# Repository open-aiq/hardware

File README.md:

# Open AIQ hardware

PCB designs (KiCad) for the Open AIQ air-quality monitor.
Firmware lives in [open-aiq/device](https://github.com/open-aiq/device); its
[`src/board.rs`](https://github.com/open-aiq/device/blob/main/src/board.rs) is the source of truth for the GPIO map.

## Layout

| Path | Contents |
| --- | --- |
| `pcb/proto2/` | Prototype 2: carrier PCB for the ESP32-S3 devkit with sensor connectors |
| `lib/` | Our own symbols and footprints, shared by every board |
| `scripts/` | `export.sh`, which builds a board's outputs from the command line |

Each PCB folder holds the KiCad project, the schematic and assembly PDFs, and
the fabrication outputs (Gerbers and BOM) under `fab/`. Its README
covers the parts, the pin map and what to check before you build.

Still to come: an SMT board with the ESP32-S3 module on it (in progress on the
`smt` branch), a battery-powered revision, and a 3D-printed enclosure.

## Working in KiCad

Everything here is a normal KiCad 10 project, and the KiCad files are the source
of truth. Open `pcb/<board>/<board>.kicad_pro` and edit the schematic and board
as you would any other design.

- **Libraries need no setup.** Our own symbols and footprints live in
  [`lib/`](lib), and each project finds them through `${KIPRJMOD}`. A part we've
  adapted, like the ESP32-S3 module with JLCPCB-sized vias, is saved there under
  its own name, so *Update footprints from library* keeps our changes.
- **Rules live in the project.** Net classes (wider power tracks), clearances and
  via sizes are set in *Board Setup*, so DRC is ready to go. The board opens
  with zero ERC and DRC messages. If you see one, it's new.
- **Outputs come from a jobset.** Open `<board>.kicad_jobset` from the project
  window (or *File → Jobsets*) and run it. It checks ERC and DRC, then writes the
  schematic PDF, an assembly drawing with every reference designator, Gerbers,
  drill files, the BOM and, for the SMT board, placement and JLCPCB BOM files.
- **The command line runs the same jobset.** From the repo root,
  `scripts/export.sh pcb/<board>` runs it with `kicad-cli`, then adds what KiCad
  doesn't make on its own: a zipped Gerber set, a JLCPCB-format placement file
  and 3D renders.

Please commit your KiCad edits and the regenerated outputs together, so the PDFs
and fab files always match the design.

## Roadmap

Planned work is tracked on the [Open AIQ Roadmap](https://github.com/orgs/open-aiq/projects/1) board.

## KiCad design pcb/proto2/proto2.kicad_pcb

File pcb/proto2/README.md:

# Proto2: devkit carrier

Proto2 is the board we use to get Open AIQ off the breadboard. The OLED sits
top-left with three buttons under it, the sensors take the middle, and your
ESP32-S3 devkit plugs into two sockets on the right with its USB port at the
bottom edge. It's single-sided (all copper on the bottom) and everything is
through-hole, so you can solder it by hand and get it made almost anywhere.

| Top | Bottom |
| --- | --- |
|  |  |

## What's on it

| Ref | Part | Wiring |
| --- | --- | --- |
| U1 | ESP32-S3-DevKitC-1, or a pin-compatible clone, on two 1×22 sockets 25.4 mm (1.0 in) apart | All signals are on the left header. USB faces the bottom edge |
| J1 | PMS5003 particulate sensor, 8-pin 1.25 mm connector | 5 V, UART on GPIO 18 (ESP TX) / 17 (ESP RX), SET on GPIO 8, RESET on GPIO 16 |
| J2 | 1.3 in SH1106 128×64 I2C OLED module, 4-pin socket | I2C, `GND VCC SCL SDA` from left to right, the order printed on the module's front. The module lies flat over the dashed OLED area |
| J3 | SHT30 breakout with 6 pins, on a 1×4 and a 1×2 socket | I2C, `VIN GND SCL SDA`. The 2 pins on the far edge (usually ADDR and ALERT) are for support only |
| SW1, SW2, SW3 | Right, left and pair buttons, 6 × 6 mm 4-leg tactile switches | GPIO 15, GPIO 6 and GPIO 7, active-low |
| R1, R2 | 4.7 kΩ I2C pull-ups | SDA (GPIO 5), SCL (GPIO 4) to 3.3 V |
| R3, R4 | 10 kΩ pull-ups | SET (R3) and RESET (R4), so the PMS5003 stays awake and out of reset unless the firmware says otherwise |
| C1–C4 | Bulk and decoupling capacitors | 47 µF + 100 nF on 5 V, 10 µF + 100 nF on 3.3 V |

The pins match [`src/board.rs`](https://github.com/open-aiq/device/blob/main/src/board.rs)
in open-aiq/device. Rev B moved several pins so every trace fits on one side of
the board, so flash firmware with the matching `board.rs` before you plug a
devkit in. Older breadboard builds used the previous map (SDA 8, SCL 9, buttons
4 and 5), which you'll find in the firmware README. A few pins are there for
later:

- **SW3 Pair (GPIO 7)** will start BLE pairing with the phone app. The firmware
  doesn't read it yet, so for now pressing it does nothing.
- **SET and RESET** have pull-ups that keep the sensor running while the
  devkit boots. The firmware drives SET low to rest the sensor between
  readings; RESET isn't driven yet.

The schematic is in [`proto2.pdf`](proto2.pdf), and [`proto2-assembly.pdf`](proto2-assembly.pdf) shows where each part goes.
Wondering why a part is there, or why it has that value?
[`proto2-rationale.pdf`](proto2-rationale.pdf) walks through every component and
pin choice, with references to the datasheets.

## Revisions

- **Rev C** (this one) rotates the OLED socket so it reads `GND VCC SCL SDA`,
  the order printed on the module. Rev B had it mirrored, which would have
  swapped 3.3 V and ground. It also widens the ground tracks where there's
  room and changes C1 from 100 µF to 47 µF. The pin map is the same as rev B.
- **Rev B** made the board single-sided, added the pair button and moved to
  today's pin map.
- **Rev A** was the first, two-layer carrier.

## Before you build

- **Check your OLED's pin order.** The socket reads `GND VCC SCL SDA` from left
  to right, and the silkscreen says so too. Hold your module face-up with its
  pins along the top: its labels should read the same. Some modules swap GND
  and VCC, and plugging one in backwards can damage it.
- **Clone devkits need the 5 V pad bridged.** Many DevKitC-1 clones have an
  `IN-OUT` solder jumper next to the 5V pin. Until you bridge it, USB power
  doesn't reach that pin, and the PMS5003 stays dark. Once it's bridged, don't
  feed 5 V into the pin while USB is plugged in.
- **The OLED lies flat over its dashed area.** It plugs into J2 face-up and
  rests over that area, which is why nothing else is placed there.
- **Measure your SHT30 before you order.** We set the gap between its two pin
  rows to 6.35 mm from a photo. If yours differs, the 4-pin row still works, and
  you can leave the 1×2 socket out.
- **The PMS5003 sits on the marked bed.** Stick it down with double-sided foam
  tape, vents facing the top edge so it doesn't pull in warm air from the
  devkit. Its case is metal, but there's no copper on top, so it can't short
  anything.
- **The devkit's antenna hangs off the top edge.** That's on purpose: copper
  under an antenna weakens WiFi and BLE, so the ground fill also stops short of
  that end.
- **R8 modules use GPIO 35, 36 and 37 for PSRAM.** Proto2 leaves them
  unconnected, so keep it that way if you add anything.
- **The status LED is on the devkit.** The firmware drives both GPIO 48
  (DevKitC-1 v1.0) and GPIO 38 (v1.1), so it lights on either. Proto2 leaves
  both pins free.

## First power-up

A few quick checks before you trust the readings:

1. **Check the PMS5003 cable with a multimeter first.** Pin 1 on the sensor
   should reach pin 1 (5 V) on J1. Some 1.25 mm cables come wired in reverse.
   That won't damage anything, but the sensor stays silent.
2. **Measure 5 V at J1 pin 1 with the fan running.** The PMS5003 needs at least
   4.5 V. A long or thin USB cable, plus the devkit's own power path, can pull
   the 5V pin below what your charger supplies.
3. **Read the serial log.** The I2C scan at boot should find `0x3C` (OLED) and
   `0x44` (SHT30).
4. **Look at the screen.** It should read upright with the pins at the top. If it
   shows upside down, the firmware's display setup notes how to flip it.

## Parts

You'll find the generated list in [`fab/proto2-bom.csv`](fab/proto2-bom.csv).
To buy them:

| Qty | Part | Notes |
| --- | --- | --- |
| 2 | 1×22 female header, 2.54 mm | Sockets for the devkit (U1) |
| 2 | 1×4 female header, 2.54 mm | OLED (J2) and SHT30 (J3) |
| 1 | 1×2 female header, 2.54 mm | SHT30's far-edge pins (J3) |
| 1 | Molex PicoBlade 53047-0810, 8-pin vertical | PMS5003 (J1). Check that it fits your sensor's cable first |
| 3 | 6 × 6 mm through-hole tactile switch, 4-leg (for example Omron B3F-1000) | SW1, SW2, SW3 |
| 2 | 4.7 kΩ resistor, 1/4 W axial | R1, R2 |
| 2 | 10 kΩ resistor, 1/4 W axial | R3, R4 |
| 1 | 47 µF electrolytic, ≥10 V, 6.3 mm radial, 2.5 mm pitch | C1 |
| 1 | 10 µF electrolytic, ≥10 V, 5 mm radial, 2 mm pitch | C3 |
| 2 | 100 nF ceramic, 5 mm pitch | C2, C4 |

## Ordering

[`fab/proto2-gerbers.zip`](fab/proto2-gerbers.zip) holds the Gerbers and
Excellon drill files: bottom copper, bottom solder mask, top silkscreen, the
outline and drills. Upload it to JLCPCB, PCBWay or a local shop as it is. We
haven't placed an order yet, so treat these settings as our first guess:

| Setting | Value |
| --- | --- |
| Size | 142 × 63 mm |
| Layers | Order it as 2-layer: you get plated holes, and the top side has pads only. The copper is all on the bottom, so a 1-layer order works too, but its holes aren't plated and the small PMS5003 connector pads lift easily when you solder them |
| Thickness | 1.6 mm |
| Min track / clearance | 0.3 / 0.25 mm (power 0.8 mm), so a track can pass between two 2.54 mm pins |
| Min hole | 0.5 mm (PMS5003 connector pins); no vias |
| Surface finish | HASL is fine |

Every part is through-hole, so there's no pick-and-place file.

## Editing

Open `proto2.kicad_pro` in KiCad 10. The repo's [Working in KiCad](../../README.md#working-in-kicad)
guide covers libraries, rules and outputs. These are ours, in [`lib/`](../../lib):

- the devkit socket and SHT30 socket footprints. The devkit socket marks its
  GND pins and its two 3V3 pins as joined inside the devkit (KiCad *jumper pad
  groups*), so they don't need tracks between them
- the arrow and phone-with-Bluetooth icons under the buttons, which are
  board-only footprints you can move
- the sensor symbols

To refresh the outputs, run `proto2.kicad_jobset` in KiCad, or this from the repo
root:

```sh
scripts/export.sh pcb/proto2
```

Both stop if ERC or DRC finds a problem.

The design rationale is written in [Typst](https://typst.app). If you change a
part, update `proto2-rationale.typ` too, then rebuild the PDF from this folder:

```sh
typst compile proto2-rationale.typ
```

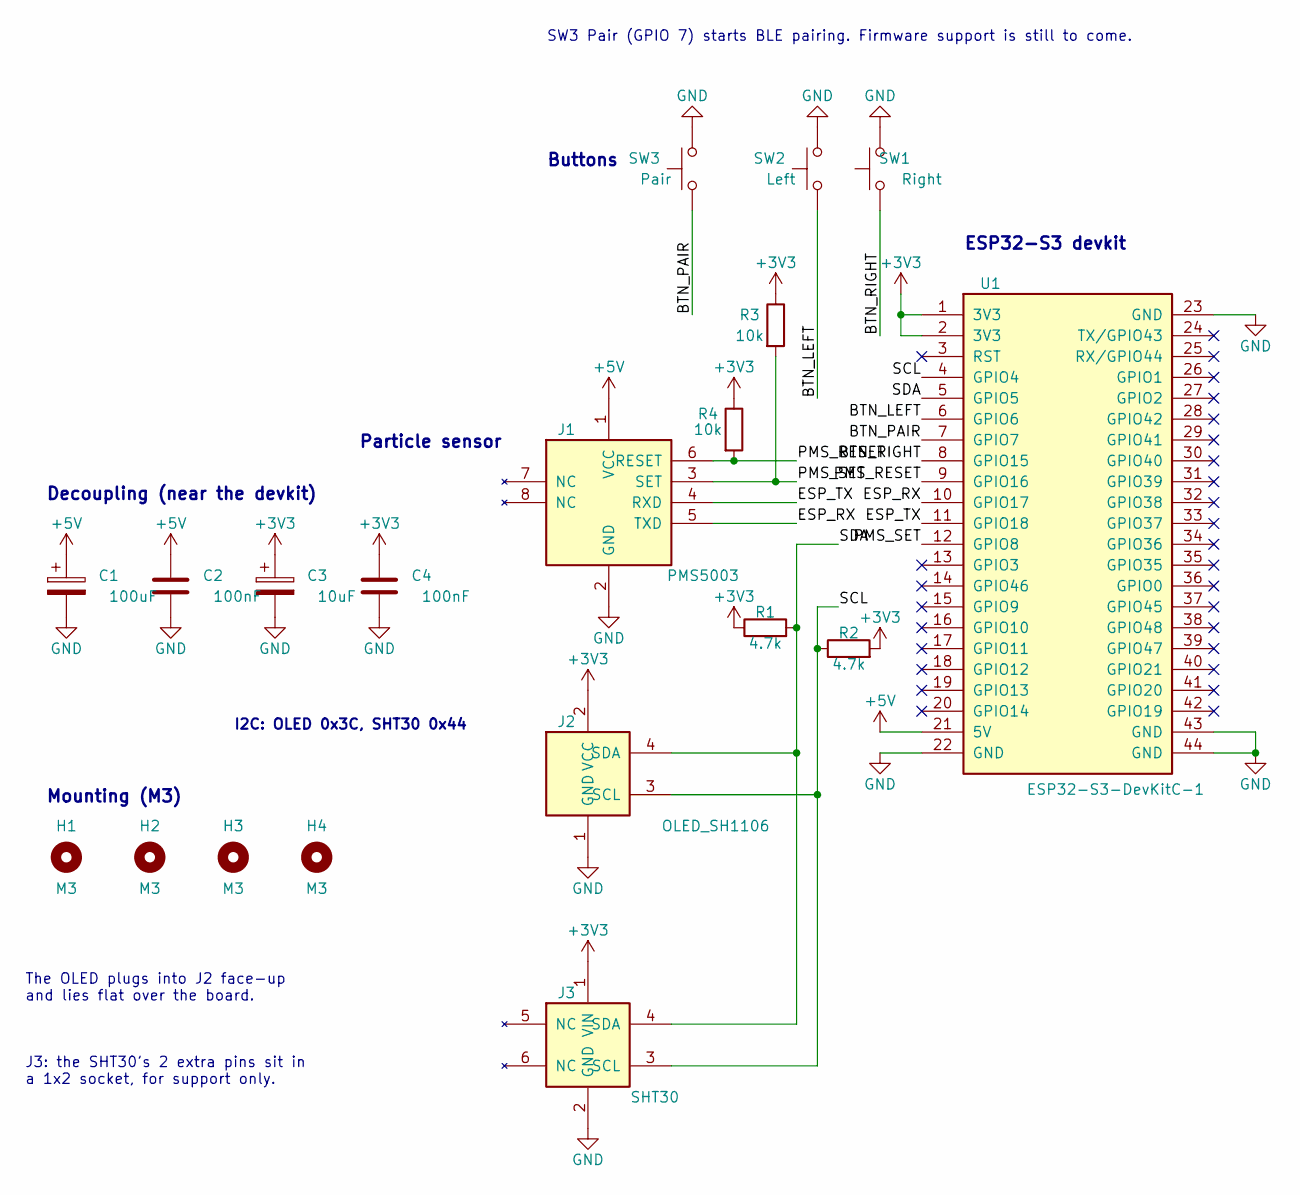
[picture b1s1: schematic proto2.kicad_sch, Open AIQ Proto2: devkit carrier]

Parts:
C1: 100uF; CP_Radial_D6.3mm_P2.50mm; Part 100 µF electrolytic, ≥10 V, 6.3 mm radi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
C2, C4: 100nF; C_Disc_D5.0mm_W2.5mm_P5.00mm; Part 100 nF ceramic, 5 mm pitch
C3: 10uF; CP_Radial_D5.0mm_P2.00mm; Part 10 µF electrolytic, ≥10 V, 5 mm radial,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
H1, H2, H3, H4: M3; MountingHole_3.2mm_M3; Part M3 mounting hole
J1: PMS5003; Molex_PicoBlade_53047-0810_1x08_P1.25mm_Vertical; Part Molex PicoBlade 53047-0810, 8-pin 1.25 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
J2: OLED_SH1106; PinSocket_1x04_P2.54mm_Vertical; Part 1×4 female header, 2.54 mm, for a 1.3 i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
J3: SHT30; SHT30_Module_Socket_4+2; Part 1×4 + 1×2 female header, 2.54 mm, for a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
R1, R2: 4.7k; R_Axial_DIN0207_L6.3mm_D2.5mm_P10.16mm_Horizontal; Part 4.7 kΩ resistor, 1/4 W axial
R3, R4: 10k; R_Axial_DIN0207_L6.3mm_D2.5mm_P10.16mm_Horizontal; Part 10 kΩ resistor, 1/4 W axial
SW1: Right; SW_PUSH_6mm; Part 6×6 mm THT tactile switch, 4-leg (e.g. 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
SW2: Left; SW_PUSH_6mm; Part 6×6 mm THT tactile switch, 4-leg (e.g. 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
SW3: Pair; SW_PUSH_6mm; Part 6×6 mm THT tactile switch, 4-leg (e.g. 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
U1: ESP32-S3-DevKitC-1; ESP32-S3-DevKitC-1_Socket; Part 2 × 1×22 female header, 2.54 mm, 25.4 m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

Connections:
+3V3: C3.1, C4.1, J2.2 (VCC), J3.1 (VIN), R1.1, R2.2, R3.1, R4.1, U1.1 (3V3), U1.2 (3V3)
+5V: C1.1, C2.1, J1.1 (VCC), U1.21 (5V)
/BTN_LEFT: SW2.1, U1.6 (GPIO6)
/BTN_PAIR: SW3.1, U1.7 (GPIO7)
/BTN_RIGHT: SW1.1, U1.8 (GPIO15)
/ESP_RX: J1.5 (TXD), U1.10 (GPIO17)
/ESP_TX: J1.4 (RXD), U1.11 (GPIO18)
/PMS_RESET: J1.6 (RESET), R4.2, U1.9 (GPIO16)
/PMS_SET: J1.3 (SET), R3.2, U1.12 (GPIO8)
/SCL: J2.3 (SCL), J3.3 (SCL), R2.1, U1.4 (GPIO4)
/SDA: J2.4 (SDA), J3.4 (SDA), R1.2, U1.5 (GPIO5)
GND: C1.2, C2.2, C3.2, C4.2, J1.2 (GND), J2.1 (GND), J3.2 (GND), SW1.2, SW2.2, SW3.2, U1.22 (GND), U1.23 (GND), U1.43 (GND), U1.44 (GND)

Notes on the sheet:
I2C: OLED 0x3C, SHT30 0x44
ESP32-S3 devkit
SW3 Pair (GPIO 7) starts BLE pairing. Firmware support is still to come.
The OLED plugs into J2 face-up and lies flat over the board.
J3: the SHT30's 2 extra pins sit in a 1x2 socket, for support only.
Buttons
Decoupling (near the devkit)
Particle sensor
Mounting (M3)

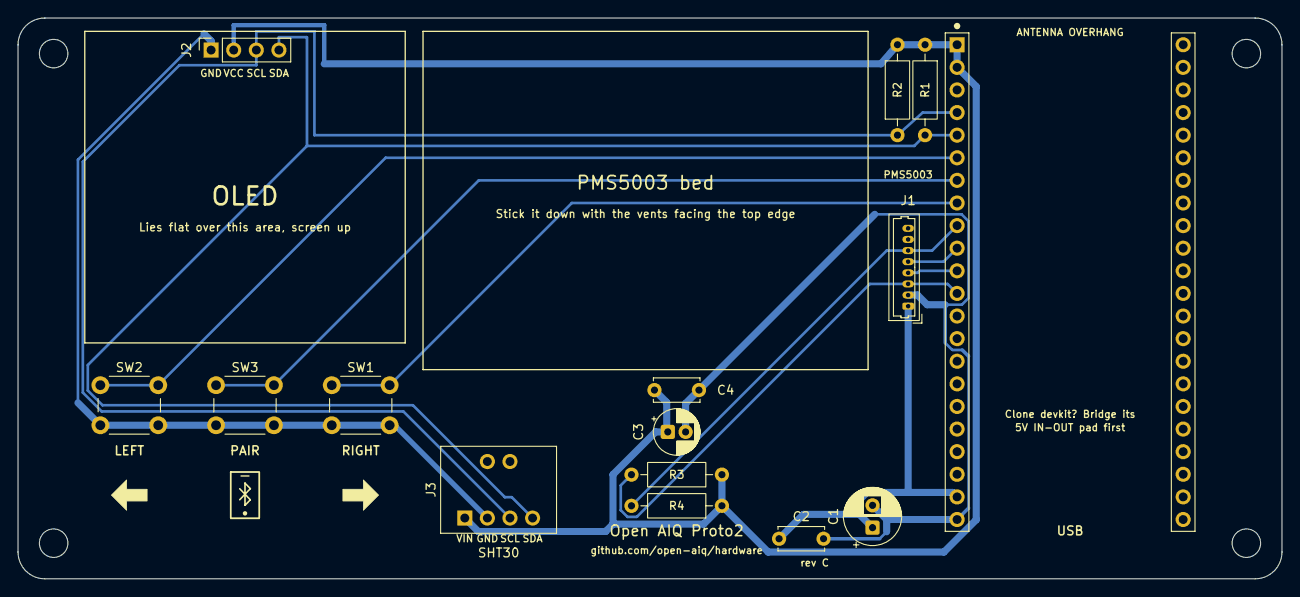
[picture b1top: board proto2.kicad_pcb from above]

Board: 2 copper layers, 142.0 x 63.0 mm, 22 parts (0 on the bottom side), 12 nets.

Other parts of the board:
G_SW1: Icon_Arrow_Right
G_SW2: Icon_Arrow_Left
G_SW3: Icon_Phone_Bluetooth

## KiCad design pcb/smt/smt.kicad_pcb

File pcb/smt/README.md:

# SMT board (rev A)

This is the first Open AIQ board with the ESP32-S3 on it, instead of on a devkit.
It does everything Proto2 does in a 56 × 44 mm board that JLCPCB can assemble
for you. You plug in the PMS5003's own cable and the OLED's Qwiic lead, and power
it from one USB-C port.

| Top | Bottom |
| --- | --- |
|  |  |

> **Status: designed, not yet ordered.** ERC and DRC pass with no errors, but no board
> has been built yet. Please read [Check before ordering](#check-before-ordering).

## What's on it

| Ref | Part | LCSC | Why |
| --- | --- | --- | --- |
| U3 | ESP32-S3-WROOM-1-N16R8 | C2913202 | Same module as the devkit: 16 MB flash, 8 MB PSRAM |
| J1 | USB-C receptacle, HRO TYPE-C-31-M-12 | C165948 | Power plus the S3's built-in USB Serial/JTAG for flashing, logs and debugging |
| U1 | USBLC6-2SC6 | C7519 | ESD protection on the USB data lines |
| F1 | 1.1 A resettable fuse (1206) | C7542963 | Protects your laptop's port if something shorts |
| U2 | AMS1117-3.3 | C6186 | 5 V to 3.3 V |
| J2 | 1.25 mm 8-pin side-entry connector | C2681529 | The PMS5003 cable from the box plugs in here |
| J3 | JST SH 4-pin (Qwiic), SM04B-SRSS-TB | C160404 | OLED on a cable: `GND 3V3 SDA SCL` |
| U4 | SHT30-DIS-B | C77361 | Temperature and humidity, on its own slotted corner |
| D1 | WS2812B-2020 | C965555 | Status LED on GPIO 48, like the devkit |
| SW1–SW4 | TS-1187A tactile switches | C318884 | RESET, BOOT, LEFT, RIGHT |

The full list is in [`fab/smt-jlc-bom.csv`](fab/smt-jlc-bom.csv). The schematic is in
[`smt.pdf`](smt.pdf), and [`smt-assembly.pdf`](smt-assembly.pdf) shows where each part goes.

### Pins

The pins match [`src/board.rs`](https://github.com/open-aiq/device/blob/main/src/board.rs)
and Proto2. SET, RESET and the LED are new, and the firmware doesn't use them yet:

| Signal | GPIO |
| --- | --- |
| I2C SDA / SCL (OLED, SHT30) | 8 / 9 |
| PMS5003 TX / RX (ESP side) | 17 / 18 |
| PMS5003 SET / RESET | 16 / 15 |
| Buttons RIGHT / LEFT | 4 / 5 |
| Status LED | 48 |
| USB D- / D+ | 19 / 20 |
| BOOT | 0 |

## Things worth knowing

- **One USB-C port does everything.** The ESP32-S3 has USB built in, so there's
  no USB-to-serial chip. Flashing, the serial console and JTAG debugging all go
  over the same cable. The firmware needs its console on USB Serial/JTAG
  (`CONFIG_ESP_CONSOLE_USB_SERIAL_JTAG`) for logs to show up.
- **The antenna hangs off the top edge.** That's on purpose: copper under the
  antenna weakens WiFi and BLE, so keep the enclosure's walls clear of it too.
- **The SHT30 sits behind a slot.** The cut-out keeps heat from the module and
  the regulator away from the sensor, so the temperature reading stays honest.
- **SET and RESET have pull-ups.** The PMS5003 keeps running if the firmware
  ignores them, and the firmware can use SET later to rest the sensor between
  readings.

## Check before ordering

We haven't built this board yet. These are the spots most likely to need a fix,
so give them a look before you place an order:

1. **PMS5003 connector fit.** C2681529 is a generic 1.25 mm side-entry header, and
   we used KiCad's Molex PicoBlade 53261 footprint for it. Compare the LCSC
   drawing with the footprint, and try the sensor's cable in a sample connector
   if you can.
2. **Part rotations in JLCPCB's preview.** KiCad and JLCPCB sometimes disagree on
   zero rotation, especially for the module, USB-C, the LED and the SOT-223
   regulator. Fix any that look turned in the assembly preview.
3. **The WS2812B runs at 3.3 V.** That keeps the data signal in spec without a
   level shifter, and it's common practice, but the LED is rated from 3.5 V.
   If it misbehaves, the fix is a 5 V supply plus a level shifter.
4. **Stock.** LCSC numbers were checked on 2026-11-08. Re-check stock when you order.

## Making it

Upload [`fab/smt-gerbers.zip`](fab/smt-gerbers.zip) to JLCPCB, turn on assembly
(top side), then add [`fab/smt-jlc-bom.csv`](fab/smt-jlc-bom.csv) and
[`fab/smt-jlc-cpl.csv`](fab/smt-jlc-cpl.csv).

| Setting | Value |
| --- | --- |
| Size | 56 × 44 mm |
| Layers | 2 |
| Thickness | 1.6 mm |
| Min track / clearance | 0.2 / 0.15 mm (power 0.4 mm) |
| Vias | 0.6 mm pad, 0.3 mm drill |
| Assembly | Top side, all parts |

## Editing

Open `smt.kicad_pro` in KiCad 10. The repo's [Working in KiCad](../../README.md#working-in-kicad)
guide covers libraries, rules and outputs. A few things specific to this board:

- **Two footprints are our own copies.** They live in [`lib/`](../../lib):
  `ESP32-S3-WROOM-1_JLC` has 0.3 mm thermal vias, and
  `USB_C_Receptacle_HRO_TYPE-C-31-M-12_BoardEdge` has its silkscreen trimmed at
  the board edge. Edit them there, not on the board.
- **The SHT30 slot has keep-out zones.** They're the rule areas along the slot on
  both copper layers, and they stop traces from crowding the cut-out. If you
  move the slot, move them too.
- **Some reference designators only show on the assembly drawing.** Five small
  parts (C5, C6, R3, R5, R6) had no room for silkscreen labels. They're
  labelled in [`smt-assembly.pdf`](smt-assembly.pdf), along with every other part.
- **The traces came from an autorouter.** Feel free to clean them up by hand.
  Keep the USB D+/D- pair short and side by side, and keep copper away from the
  antenna edge.

To refresh the outputs, run the jobset in KiCad, or this from the repo root:

```sh
RENDER_ZOOM=1.15 scripts/export.sh pcb/smt
```

The board was first laid out by scripts. They're in this repo's history (commit
`fc827ce`, `pcb/smt/tools/`), but the KiCad files have moved on since, so don't
re-run them.

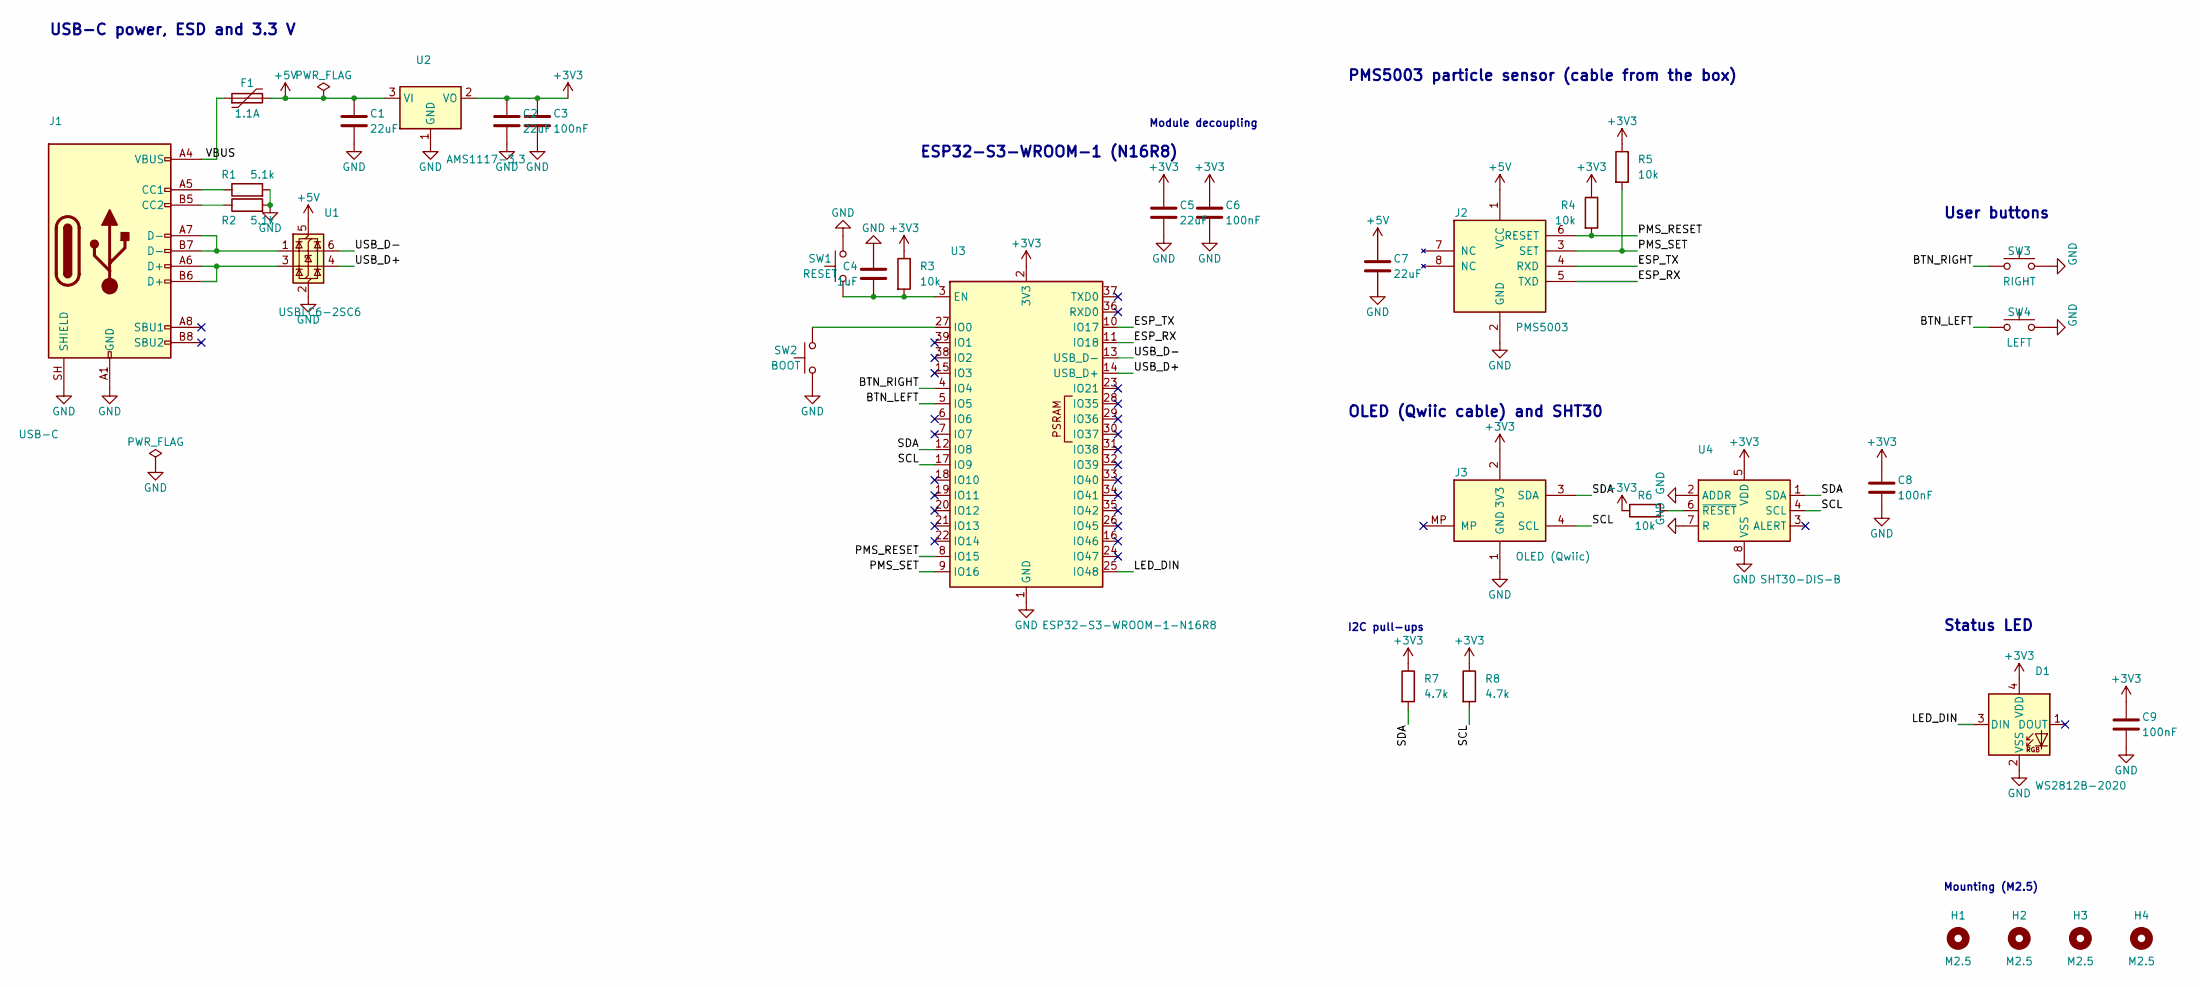
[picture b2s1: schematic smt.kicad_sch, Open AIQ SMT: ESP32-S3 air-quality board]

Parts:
C1, C2, C5, C7: 22uF; C_0805_2012Metric; LCSC C45783
C3, C6, C8, C9: 100nF; C_0603_1608Metric; LCSC C14663
C4: 1uF; C_0603_1608Metric; LCSC C15849
D1: WS2812B-2020; LED_WS2812B-2020_PLCC4_2.0x2.0mm; LCSC C965555
F1: 1.1A; Fuse_1206_3216Metric; LCSC C7542963
H1, H2, H3, H4: M2.5; MountingHole_2.7mm_M2.5
J1: USB-C; USB_C_Receptacle_HRO_TYPE-C-31-M-12_BoardEdge; LCSC C165948
J2: PMS5003; Molex_PicoBlade_53261-0871_1x08-1MP_P1.25mm_Horizontal; LCSC C2681529
J3: OLED (Qwiic); JST_SH_SM04B-SRSS-TB_1x04-1MP_P1.00mm_Horizontal; LCSC C160404
R1, R2: 5.1k; R_0603_1608Metric; LCSC C23186
R3, R4, R5, R6: 10k; R_0603_1608Metric; LCSC C25804
R7, R8: 4.7k; R_0603_1608Metric; LCSC C23162
SW1: RESET; SW_Push_1P1T_XKB_TS-1187A; LCSC C318884
SW2: BOOT; SW_Push_1P1T_XKB_TS-1187A; LCSC C318884
SW3: RIGHT; SW_Push_1P1T_XKB_TS-1187A; LCSC C318884
SW4: LEFT; SW_Push_1P1T_XKB_TS-1187A; LCSC C318884
U1: USBLC6-2SC6; SOT-23-6; LCSC C7519
U2: AMS1117-3.3; SOT-223-3_TabPin2; LCSC C6186
U3: ESP32-S3-WROOM-1-N16R8; ESP32-S3-WROOM-1_JLC; LCSC C2913202
U4: SHT30-DIS-B; Sensirion_DFN-8-1EP_2.5x2.5mm_P0.5mm_EP1.1x1.7mm; LCSC C77361

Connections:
+3V3: C2.1, C3.1, C5.1, C6.1, C8.1, C9.1, D1.4 (VDD), J3.2 (3V3), R3.1, R4.1, R5.1, R6.1, R7.1, R8.1, U2.2 (VO), U3.2 (3V3), U4.5 (VDD)
+5V: C1.1, C7.1, F1.2, J2.1 (VCC), U1.5 (VBUS), U2.3 (VI)
/BTN_LEFT: SW4.1, U3.5 (IO5)
/BTN_RIGHT: SW3.1, U3.4 (IO4)
/ESP_RX: J2.5 (TXD), U3.11 (IO18)
/ESP_TX: J2.4 (RXD), U3.10 (IO17)
/LED_DIN: D1.3 (DIN), U3.25 (IO48)
/PMS_RESET: J2.6 (RESET), R4.2, U3.8 (IO15)
/PMS_SET: J2.3 (SET), R5.2, U3.9 (IO16)
/SCL: J3.4 (SCL), R8.2, U3.17 (IO9), U4.4 (SCL)
/SDA: J3.3 (SDA), R7.2, U3.12 (IO8), U4.1 (SDA)
/USB_D+: U1.4 (I/O2), U3.14 (USB_D+)
/USB_D-: U1.6 (I/O1), U3.13 (USB_D-)
/VBUS: F1.1, J1.A4 (VBUS), J1.A9 (VBUS), J1.B4 (VBUS), J1.B9 (VBUS)
GND: C1.2, C2.2, C3.2, C4.1, C5.2, C6.2, C7.2, C8.2, C9.2, D1.2 (VSS), J1.A1 (GND), J1.A12 (GND), J1.B1 (GND), J1.B12 (GND), J1.SH (SHIELD), J2.2 (GND), J3.1 (GND), R1.2, R2.2, SW1.2, SW2.1, SW3.2, SW4.2, U1.2 (GND), U2.1 (GND), U3.1 (GND), U3.40 (GND), U3.41 (GND), U4.2 (ADDR), U4.7 (R), U4.8 (VSS), U4.9 (VSS)
unnamed: J1.A5 (CC1), R1.1
unnamed: J1.B5 (CC2), R2.1
unnamed: J1.A6 (D+), J1.B6 (D+), U1.3 (I/O2)
unnamed: J1.A7 (D-), J1.B7 (D-), U1.1 (I/O1)
unnamed: C4.2, R3.2, SW1.1, U3.3 (EN)
unnamed: SW2.2, U3.27 (IO0)
unnamed: R6.2, U4.6 (~RESET)

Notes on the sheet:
USB-C power, ESD and 3.3 V
PMS5003 particle sensor (cable from the box)
Module decoupling
Status LED
I2C pull-ups
Mounting (M2.5)
User buttons
OLED (Qwiic cable) and SHT30
ESP32-S3-WROOM-1 (N16R8)

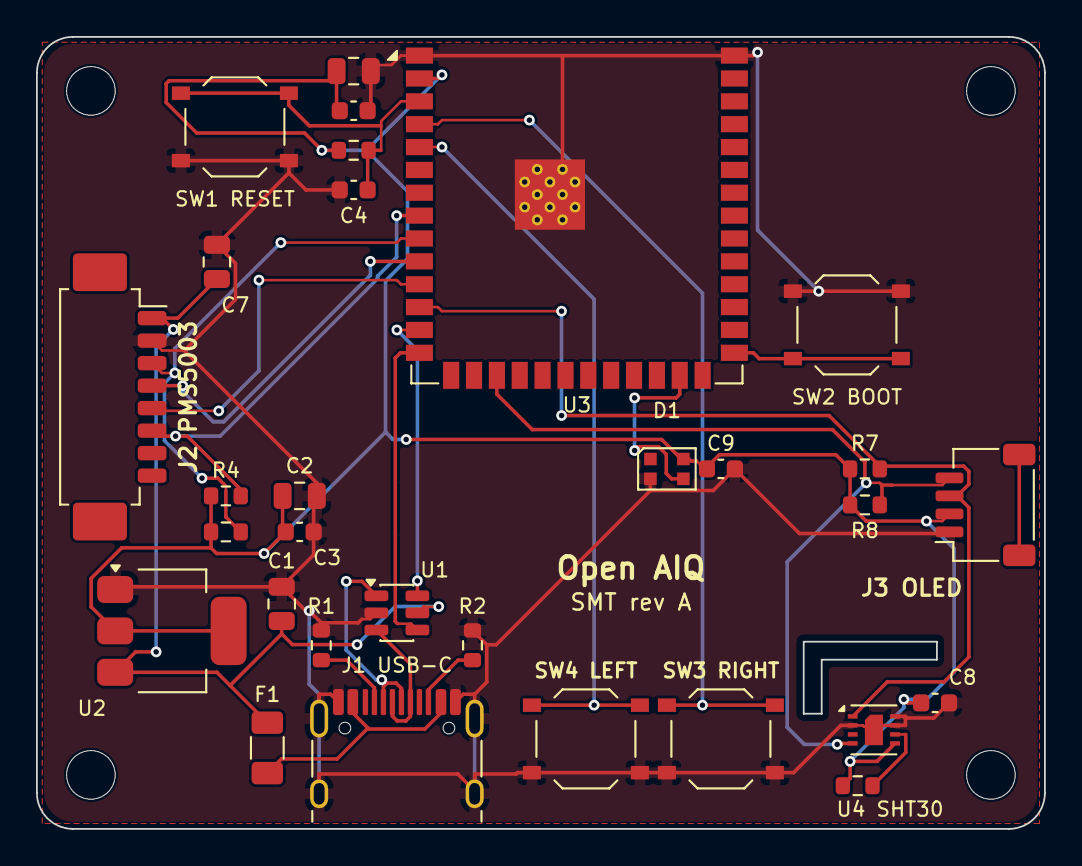
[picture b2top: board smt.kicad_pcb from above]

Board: 2 copper layers, 56.0 x 44.0 mm, 34 parts (0 on the bottom side), 22 nets.

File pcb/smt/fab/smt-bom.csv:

"Reference","Value","Footprint","Qty","LCSC","Datasheet"
"C1,C2,C5,C7","22uF","Capacitor_SMD:C_0805_2012Metric","4","C45783",""
"C3,C6,C8,C9","100nF","Capacitor_SMD:C_0603_1608Metric","4","C14663",""
"C4","1uF","Capacitor_SMD:C_0603_1608Metric","1","C15849",""
"D1","WS2812B-2020","LED_SMD:LED_WS2812B-2020_PLCC4_2.0x2.0mm","1","C965555",""
"F1","1.1A","Fuse:Fuse_1206_3216Metric","1","C7542963",""
"J1","USB-C","Connector_USB:USB_C_Receptacle_HRO_TYPE-C-31-M-12","1","C165948",""
"J2","PMS5003","Connector_Molex:Molex_PicoBlade_53261-0871_1x08-1MP_P1.25mm_Horizontal","1","C2681529",""
"J3","OLED (Qwiic)","Connector_JST:JST_SH_SM04B-SRSS-TB_1x04-1MP_P1.00mm_Horizontal","1","C160404",""
"R1,R2","5.1k","Resistor_SMD:R_0603_1608Metric","2","C23186",""
"R3-R6","10k","Resistor_SMD:R_0603_1608Metric","4","C25804",""
"R7,R8","4.7k","Resistor_SMD:R_0603_1608Metric","2","C23162",""
"SW1","RESET","Button_Switch_SMD:SW_Push_1P1T_XKB_TS-1187A","1","C318884",""
"SW2","BOOT","Button_Switch_SMD:SW_Push_1P1T_XKB_TS-1187A","1","C318884",""
"SW3","RIGHT","Button_Switch_SMD:SW_Push_1P1T_XKB_TS-1187A","1","C318884",""
"SW4","LEFT","Button_Switch_SMD:SW_Push_1P1T_XKB_TS-1187A","1","C318884",""
"U1","USBLC6-2SC6","Package_TO_SOT_SMD:SOT-23-6","1","C7519",""
"U2","AMS1117-3.3","Package_TO_SOT_SMD:SOT-223-3_TabPin2","1","C6186",""
"U3","ESP32-S3-WROOM-1-N16R8","RF_Module:ESP32-S3-WROOM-1","1","C2913202","https://www.espressif.com/sites/default/files/documentation/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"
"U4","SHT30-DIS-B","Sensor_Humidity:Sensirion_DFN-8-1EP_2.5x2.5mm_P0.5mm_EP1.1x1.7mm","1","C77361",""

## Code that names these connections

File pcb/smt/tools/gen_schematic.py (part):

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     lcsc="C2681529", refpos=(261.62, 64.77, "left"), valpos=(271.78, 83.82, "left"))
pwr("+5V", PX, 60.96); pwr("GND", PX, 86.36)
PR = PX + 12.7
wire((PR, 68.58), (284.48, 68.58), (292.1, 68.58)); junc(284.48, 68.58); label("PMS_RESET", 292.1, 68.58)
wire((PR, 71.12), (289.56, 71.12), (292.1, 71.12)); junc(289.56, 71.12); label("PMS_SET", 292.1, 71.12)
wire((PR, 73.66), (292.1, 73.66)); label("ESP_TX", 292.1, 73.66)
wire((PR, 76.2), (292.1, 76.2)); label("ESP_RX", 292.1, 76.2)
R("R4", "10k", 284.48, 64.77, refpos=(281.94, 63.5, "right"), valpos=(281.94, 66.04, "right")); pwr("+3V3", 284.48, 60.96)
R("R5", "10k", 289.56, 57.15); pwr("+3V3", 289.56, 53.34)
wire((289.56, 60.96), (289.56, 71.12))       # R5 lead crosses PMS_RESET without connecting
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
